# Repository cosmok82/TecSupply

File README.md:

TecSupply
=====

<div style="text-align: center;">

</div>
<br>
Author: Cosimo Orlando.<br>
Blog: http://creativityslashdesign.tk/
<br>
<br>
TecSupply, a 5$ OTG-Charging cable for Teclast tablets.
<br>
All info on my blog.
<br>
<br>
<br>
GPL v3 License

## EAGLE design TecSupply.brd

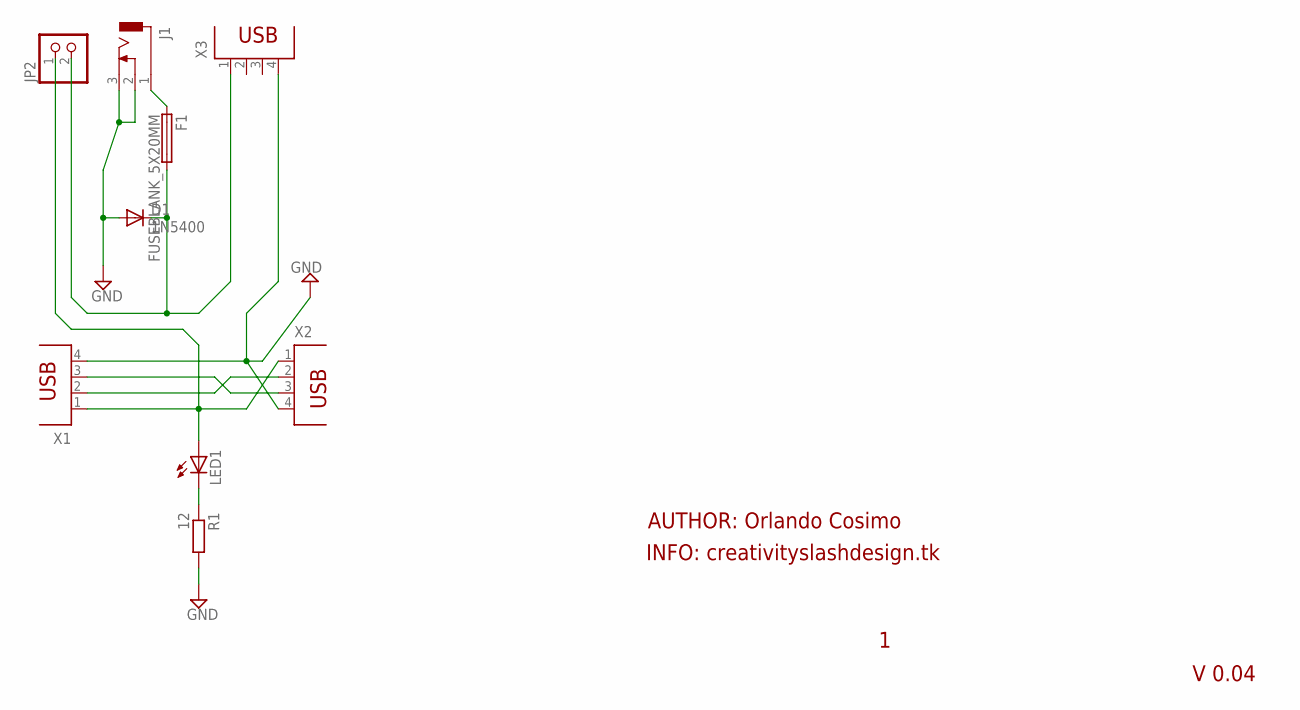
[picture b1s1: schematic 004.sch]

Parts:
D1: 1N5400; DO201-15
F1: FUSEBLANK_5X20MM; FUSE_HOLDER_5X20MM
J1: DCJ0303
JP2: PINHD-1X2/90; 1X02/90
LED1: LED5MM
R1: 12; 0204/7
X1, X2, X3: PN87520

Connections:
GND: D1.A, J1.2, J1.3, R1.2, X1.4, X2.4, X3.4
unnamed: F1.1, J1.1
unnamed: JP2.1, LED1.A, X1.1, X2.1
unnamed: X1.2, X2.2
unnamed: X1.3, X2.3
unnamed: D1.C, F1.2, JP2.2, X3.1
unnamed: LED1.K (C), R1.1

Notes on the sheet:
V 0.04
INFO: creativityslashdesign.tk
AUTHOR: Orlando Cosimo

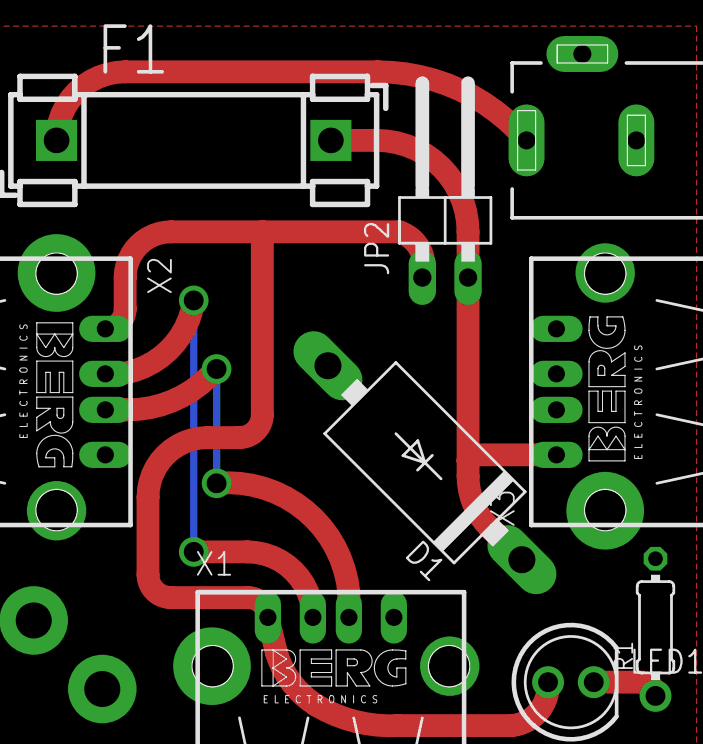
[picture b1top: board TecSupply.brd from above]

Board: 2 copper layers, 9 parts (0 on the bottom side), 7 nets.

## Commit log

2015-04-04 :octocat: Added .gitattributes & .gitignore files
2015-04-04 Release 04/04/2015
2015-04-04 reapair
2015-04-04 rename
